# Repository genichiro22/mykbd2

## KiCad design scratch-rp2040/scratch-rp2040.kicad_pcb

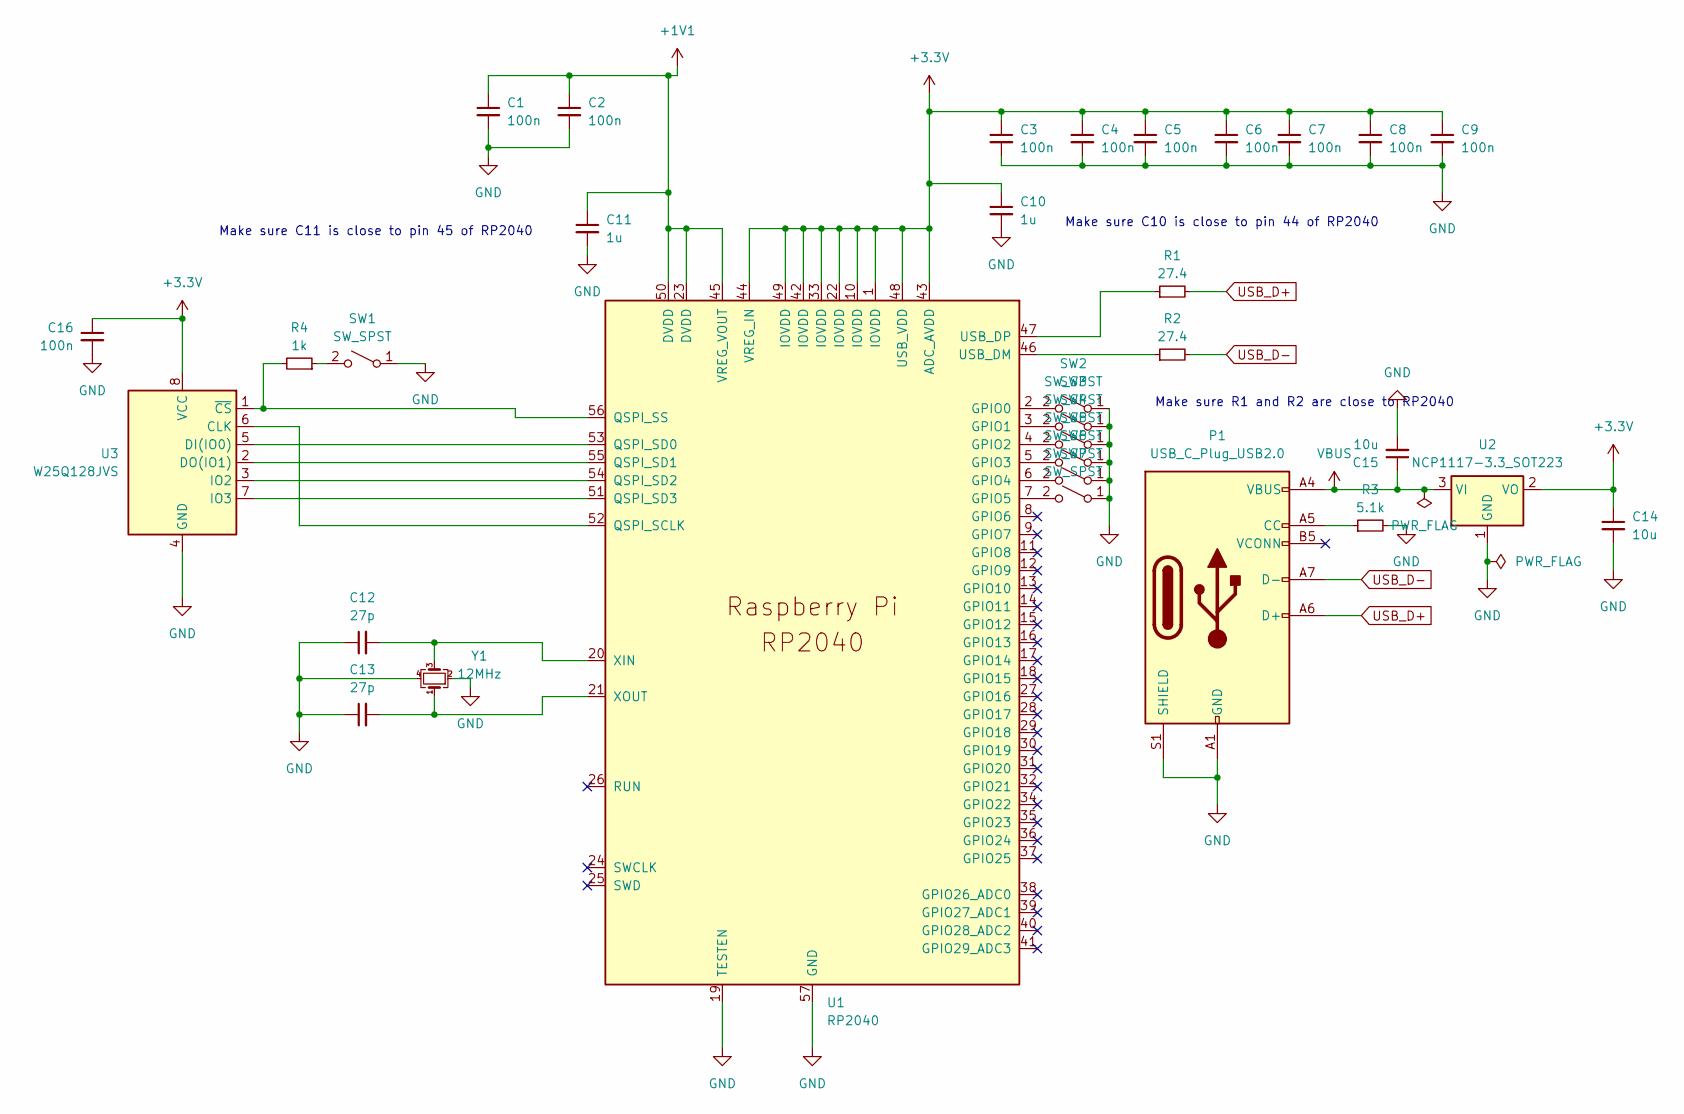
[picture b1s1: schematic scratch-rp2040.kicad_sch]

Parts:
C1, C2, C3, C4, C5, C6, C7, C8, C9, C16: 100n; C_0201_0603Metric
C10, C11: 1u; C_0201_0603Metric
C12, C13: 27p; C_0201_0603Metric
C14, C15: 10u; C_0402_1005Metric
P1: USB_C_Plug_USB2.0; USB_C_Receptacle_G-Switch_GT-USB-7010ASV
R1, R2: 27.4; R_0201_0603Metric
R3: 5.1k; R_0201_0603Metric
R4: 1k; R_0201_0603Metric
SW1: SW_SPST; SW_SPDT_PCM12
SW2, SW3, SW4, SW5, SW6, SW7: SW_SPST; SW_SPST_B3U-1000P
U1: RP2040; QFN-56-1EP_7x7mm_P0.4mm_EP3.2x3.2mm
U2: NCP1117-3.3_SOT223; SOT-223-3_TabPin2
U3: W25Q128JVS; SOIC-8_5.23x5.23mm_P1.27mm
Y1: 12MHz; Crystal_SMD_3225-4Pin_3.2x2.5mm

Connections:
+1V1: C1.1, C2.1, C11.1, U1.23 (DVDD), U1.45 (VREG_VOUT), U1.50 (DVDD)
+3.3V: C3.1, C4.1, C5.1, C6.1, C7.1, C8.1, C9.1, C10.1, C14.1, C16.1, U1.1 (IOVDD), U1.10 (IOVDD), U1.22 (IOVDD), U1.33 (IOVDD), U1.42 (IOVDD), U1.43 (ADC_AVDD), U1.44 (VREG_IN), U1.48 (USB_VDD), U1.49 (IOVDD), U2.2 (VO), U3.8 (VCC)
GND: C1.2, C2.2, C3.2, C4.2, C5.2, C6.2, C7.2, C8.2, C9.2, C10.2, C11.2, C12.1, C13.1, C14.2, C15.2, C16.2, P1.A1 (GND), P1.A12 (GND), P1.B1 (GND), P1.B12 (GND), P1.S1 (SHIELD), R3.2, SW1.1 (A), SW2.1 (A), SW3.1 (A), SW4.1 (A), SW5.1 (A), SW6.1 (A), SW7.1 (A), U1.19 (TESTEN), U1.57 (GND), U2.1 (GND), U3.4 (GND), Y1.2, Y1.4
unnamed: P1.A5 (CC), R3.1
unnamed: R4.1, SW1.2 (B)
unnamed: SW2.2 (B), U1.2 (GPIO0)
unnamed: SW3.2 (B), U1.3 (GPIO1)
unnamed: SW4.2 (B), U1.4 (GPIO2)
unnamed: SW5.2 (B), U1.5 (GPIO3)
unnamed: SW6.2 (B), U1.6 (GPIO4)
unnamed: SW7.2 (B), U1.7 (GPIO5)
unnamed: U1.52 (QSPI_SCLK), U3.6 (CLK)
unnamed: U1.53 (QSPI_SD0), U3.5 (DI(IO0))
unnamed: U1.55 (QSPI_SD1), U3.2 (DO(IO1))
unnamed: U1.54 (QSPI_SD2), U3.3 (IO2)
unnamed: U1.51 (QSPI_SD3), U3.7 (IO3)
unnamed: R4.2, U1.56 (QSPI_SS), U3.1 (~CS)
unnamed: R2.1, U1.46 (USB_DM)
unnamed: R1.1, U1.47 (USB_DP)
unnamed: C12.2, U1.20 (XIN), Y1.3
unnamed: C13.2, U1.21 (XOUT), Y1.1
USB_D+: P1.A6 (D+), R1.2
USB_D-: P1.A7 (D-), R2.2
VBUS: C15.1, P1.A4 (VBUS), P1.A9 (VBUS), P1.B4 (VBUS), P1.B9 (VBUS), U2.3 (VI)

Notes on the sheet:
Make sure R1 and R2 are close to RP2040
Make sure C10 is close to pin 44 of RP2040
Make sure C11 is close to pin 45 of RP2040

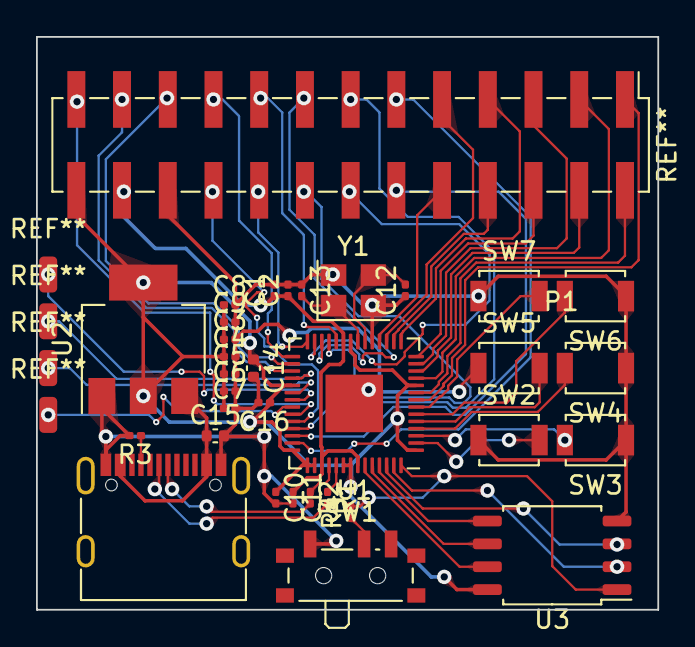
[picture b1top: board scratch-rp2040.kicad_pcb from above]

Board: 2 copper layers, 34.5 x 31.8 mm, 32 parts (0 on the bottom side), 24 nets.

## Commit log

2023-09-16 rp2040 added
2023-09-17 schematic ended
2023-09-18 footprint assigned
2023-09-18 categorized footprints
2023-09-18 wiring completed
2023-09-18 pcb wiring including switches
2023-09-20 footprint updated, looking jlcpcb assembly parts lib
2023-09-20 usb receptacle changed
2023-09-20 parts placed
2023-09-20 parts placement considering...
2023-09-21 wiring finished
2023-09-21 wired GPIOs remained
